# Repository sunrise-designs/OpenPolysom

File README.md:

.png)

OpenPolysom
===========================

This is an open-source Polysomnography (PSG) physical device and analysis software. It performs what is know as a sleep study.

It runs on an ESP32 microcontroller, and collects these signals from a patient:
- [Respiratory Inductance Plethysmography (RIP)](#baseline-removal-from-the-rip-signal---the-chest-belts)
- [Nasal air flow rate](#air-flow-signal-processing)
- RR intervals (heart rate)
- Sound recording for [snoring detection](#snoring-classification-and-feature-extraction)
- Acceleration data from the leg sensors to [detect leg twitching](#accelerometer-data-processing)

New! Some real recordings:
===========================
[A somewhat truncated 2 hours of real sleep data - 17 July 2026](https://polysom.netlify.app/index.html?meta=studies%2Fbiometric_2026-07-16_23-00-00%2Fmeta.json)

Why do this?
===========================
It's about creating an _accessible, rapid_ diagnostic pathway for sleep disorders. Many, many people suffer from sleep disorders, breathing-related ones in particular. They have a significant effect on the quality of life, safety (falling asleep while driving) and serious long-term adverse health effects.
The current diagnostic process is abysmally slow on the NHS. There are private routes, but they are financially prohibitive for most.

It's hard to diagnose because:
- Most of the time, the sufferer is unaware of the problem (they only know they are groggy and tired)
- Partners don't know how to tell "normal" snoring, if there's such a thing, from a serious breathing-related sleep disorder
- It's seen as a "specialist" subject in the NHS, and GPs receive hardly any training in this field. They are quick to dismiss fatigue-related complaints
- Even once the person starts looking for a cause, the different avenues to explore are bewildering, expensive, and full of marketing hype
- There is not a streamlined diagnostic pathway, or "one-size-fits-all" solution, because of individual anatomy, neurological comorbidities, lifestyle and so on

What does this aim to do?
===========================
Firstly, this is not a replacement for a qualified medical opinion and treatment.
However, this seeks to:
- Raise awareness. There's not enough awareness around the variety of sleep disorders in the population. There have been huge campaigns around cancers, heart health (which is fantastic), but not this, yet
- Open source, forever. The main, explicit intention of this project is to always remain fully open source, software and hardware
  This means that anyone with enough knowledge can look at data, contribute, validate and build the OpenPolysom
- It aims to be simple enough for a layman to use, but powerful enough for advanced research and clinical diagnostics
- Affordable. There are great polysomnography solutions out there, sure. But they are very expensive, proprietary, and generally only accessible to
state healthcare systems or private clinics. The goal of this project is to be financially affordable to anyone

What is this going to look like?
===========================
The eventual goal is to have an easy-to-use, reusable, affordable polysomnography device and diagnostic infrastructure.
- A patient receives the device, or even builds it themselves
- They wear it for one or more nights
- Quality pre-processed data is recorded onto the device (removable SD card)
- There could be a few ways to analyze the data:
    - Send it to a specialist doctor or a clinician
    - Ask for advice on peer-to-peer forums like Apnea Board
    - Some combination of local and cloud-based algorithm can detect features of a number of breathing-related sleep disorders, like Obstructive Apnea, Central Apnea, UARS, and so on
- The strength of this project is pulling together various bits of science which are out there, but disjoint and difficult to find and use. It aims to make a comprehensive assessment of the data, find a possible problem (if any) and at least suggest possible treatment pathways. This is in no way a substitute for qualified medical advice.

How can it detect sleep disorders?
===========================
It a basic level, it's not so difficult! (The following is a simplified version!)

- If you're snoring away, then you stop, your chest belts show that you are "paradoxically breathing", in other words heaving for air, but there's no airflow - you might have Obstructive Apnea. You tongue or soft palate have collapsed backwards and blocked your airway. Your blood oxygen will also drop.
- There's no airflow, _and_ the chest belts show no movement. Your brain simply "forgot" to breathe! That's Central Apnea. Your blood oxygen wil also drop.
- Your blood oxygen does not drop appreciably, but your heart rate spikes significantly at times during your sleep. Your body has become quite sensitive to "breathing effort", and even though your airway isn't fully obstructed, your sleep is fragmented enough to make you feel terrible. This might be Upper Airway Resistance Syndrome (UARS). You might a completely "healthy" score on an official sleep apnea scale, but this is still a very serious problem!
- Your breathing might be fine, but you twitch lots in your sleep (this can be detected by an accelerometer). This could be Periodic Limb Movement Disorder (PLMD). This can also make you feel very tired.
- You might have none of the above, but you wake up gasping, talking and screaming in your sleep. You might be suffering from nightmares!
- And so on!

The point it, it takes a confluence of all the different signals recorded by the polysomnography device to steer the diagnosis in the correct direction. Recording just one or two things usually is not enough.

Challenges to solve
===========================
## Medical device compliance

There is no getting around the fact that this is a Medical Device, likely class B. There is no point in simply providing a heap of dry statistics and numerical metrics from the recorded signals - 99% of users without a very specialist skill set would not be able to interpret them. This isn't a "wellness" device. The interpretation is the whole point of the OpenPolysom, being able to cautiously point the user in the right direction on their path to the eventual resolution of their sleep problems.
This lands it firmly in the regulated territory. Therefore, this system, software and hardware alike, will be designed with IEC 62304 (Medical Software) in mind. The intent is to keep the code which extracts the dry metrics completely separate from the code which makes any interpretation of those metrics.

## Accelerometer data processing
I am currently using two accelerometers attached near the ankle to both legs to detect leg twitching and decide whether PLMS (Periodic Limb Movements of Sleep) or PLMD (Periodic Limb Movement Disorder) is present. The American Academy of Sleep Medicine (AASM) scoring criteria are fairly straightforward to interpret, but for an accurate count the acceleration due to twitching (sudden movement followed by return to the same leg position) should be distinguished from the acceleration due to the position change. This will be determined by the angle between the two baseline positions $q1$ and $q2$: $\Delta q = q_2 \otimes q_1^{-1}$ being below a certain threshold. (note: for advanced clinical studies, Leg Movement events are detected with Electromyography (EMG), because isometric contractions which do not result in physical movement also count. The accelerometers is a temporary proxy which is easier to setup and more robust)

## Baseline removal from the RIP signal - the chest belts

The plan is to achieve that using a combination of Qualitative Diagnostic Calibration (QDC) variant (Marvin Sackner, 1989) and Adaptive Iteratively Reweighted Penalized Least Squares (airPLS)

## Snoring classification and feature extraction

The end game would be to achieve accurate classification of anatomical snoring site according to the VOTE (Velum, Oropharynx, Tongue base, and Epiglottis). This could be achieved using MFCC/Mel feature extraction, then a fast real time ML model trained on the MPSSC (Munich-Passau Snore Sound Corpus) data.

## Air flow signal processing

I have not yet recorded a sample signal, but I am guessing there will be pretty standard noise filtering involved

The wiki — an LLM-first knowledge base
===========================
The in-depth documentation lives in an **LLM wiki**: a structured knowledge base written first for AI coding agents to read as working context, and second for humans. It is deliberately [`llms.txt`](https://llmstxt.org/)-shaped — a curated *map* of the project (architecture, data formats, signal processing, settled decisions, roadmap, coding standards) rather than an exhaustive dump — so an agent (or a person) reads the index first and then opens only the pages a task needs. The same Markdown is browsable as a website.

- **Browse it online:** https://sunrise-designs.github.io/OpenPolysom/
- **Read the source:** [`wiki/INDEX.md`](wiki/INDEX.md) — start here
- **Jump straight in:** [architecture](wiki/knowledge/architecture.md) · [data formats](wiki/knowledge/data-formats.md) · [roadmap](wiki/state/roadmap.md)

The Markdown in [`wiki/`](wiki) is rendered to a static site with [Quartz](https://quartz.jzhao.xyz/) and published to GitHub Pages (build: [`web/build.sh`](web/build.sh)).

What hardware does this expect
----------------------------
The hardware is currently a breadboard prototype, however a custom PCB is being developed in Kicad. See [hardware](/Hardware) folder.

The breadboard features (for now)
- LDC1612 inductance-to-frequency sensor on I2C bus with address 0x2B
- SDP800-125Pa Digital DP sensor (±125 Pa) (I2C address 0x25 or 0x26)
- Two MMA8451 accelerometers (with different I2C addresses)
- Polar H9 heart rate sensor via BLE

How to build
----------------------------
This is work in progress as project is developing fast.

The basic dependencies are:
- Python
- npm
- esp-idf (v 6.0 onwards)
- Rust (upcoming)

How to use
----------------------------
See this [brief guide](how%20to%20use.md)

Why a Som?
===========================
"Som" is a shorthand for polysomnography, and "Som" in Russian is a Wels catfish, _Silurus glanis_. I think it looks cool and terrifying in equal measure. Its whiskers also make me think of all the various probes and electrodes which feature on a polysomnography machine.

Disclaimer
===========================
This software is for informational and educational purposes only. It is not a medical device and is not intended to diagnose, treat, cure, or prevent any disease or sleep disorder.

Not Professional Advice: The outputs generated by this software should not be used as a substitute for professional medical advice, diagnosis, or treatment.

Consult a Physician: Always seek the advice of a qualified healthcare provider with any questions you may have regarding a medical condition.

No Liability: The developers and contributors provide this software "as is" and are not responsible for any actions taken based on its results.

References and inspiration
===========================
This software uses (heavily modified)
https://github.com/Seeed-Studio/Seeed_LDC1612

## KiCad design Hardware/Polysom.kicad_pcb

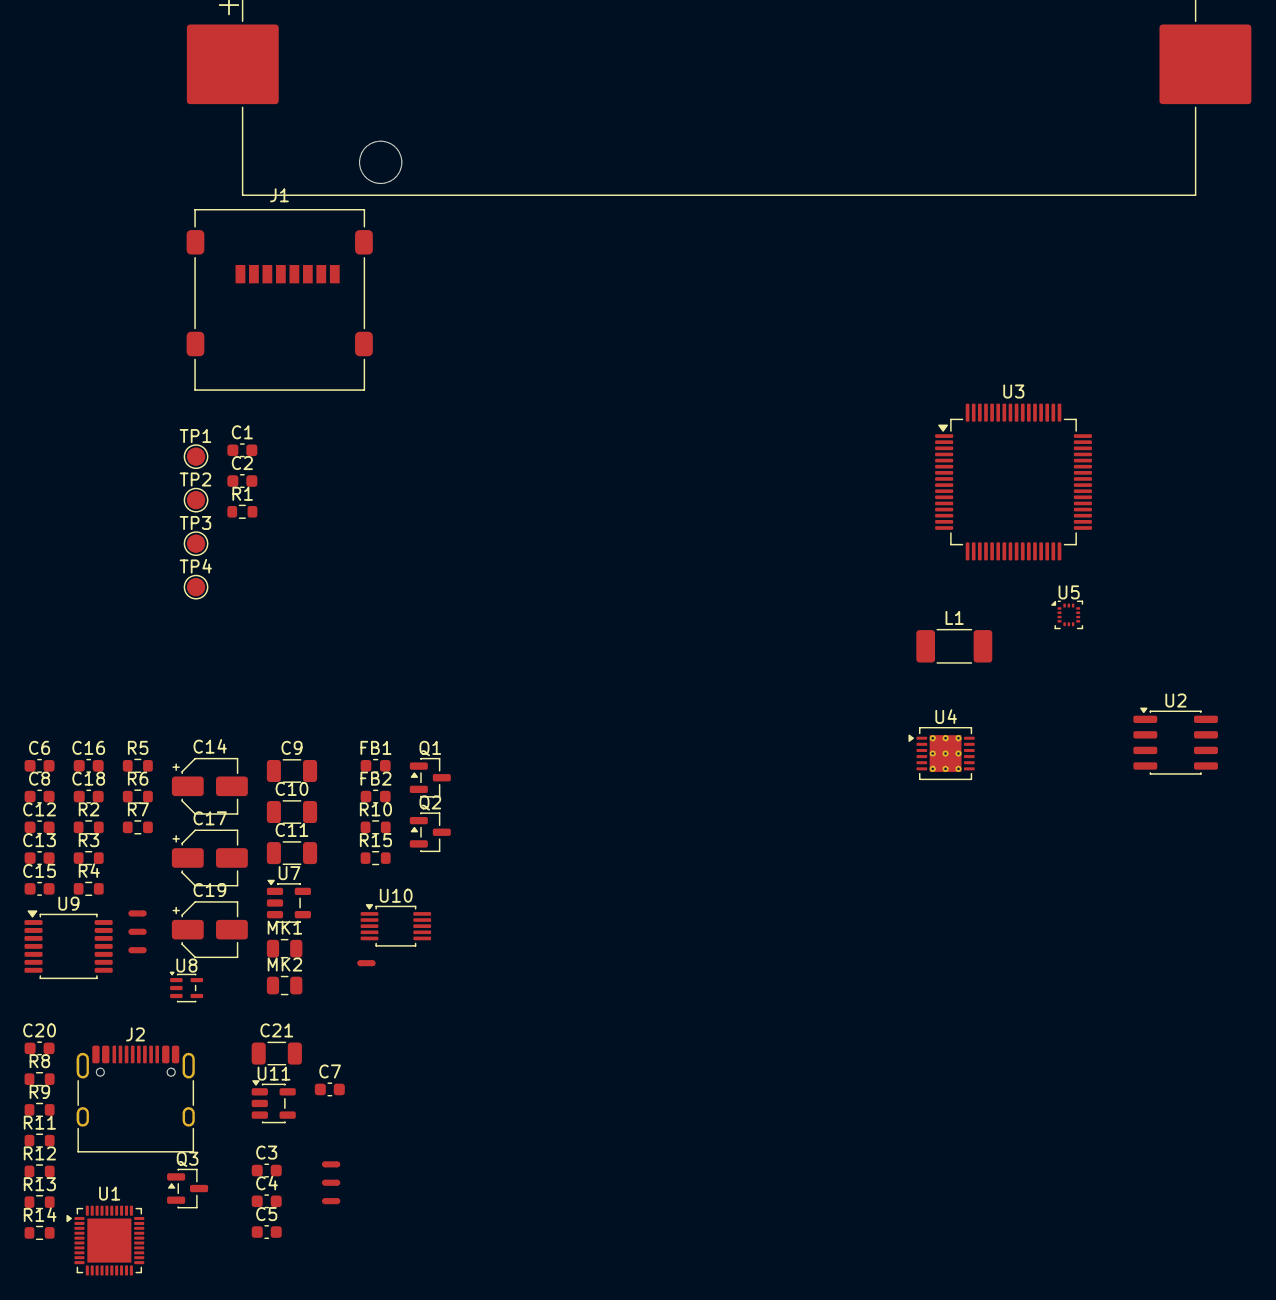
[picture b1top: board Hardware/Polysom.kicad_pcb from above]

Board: 2 copper layers, 68 parts (0 on the bottom side), 42 nets, no tracks yet.

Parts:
BT1: 18650; BatteryHolder_Keystone_1042_1x18650
C1, C2, C12, C13: C; C_0603_1608Metric
C3, C4, C8, C15, C16, C18, C20: 100n; C_0603_1608Metric
C5: 10u; C_0603_1608Metric
C6, C7: 470p; C_0603_1608Metric
C9, C10, C11, C21: 1u; C_1206_3216Metric
C14, C17, C19: 10u; CP_Elec_4x5.4
FB1, FB2: FerriteBead; L_0603_1608Metric
J1: Micro_SD_Card 693072010801; microSD_HC_Molex_47219-2001
J2: USB_C_Receptacle; USB_C_Receptacle_HRO_TYPE-C-31-M-12
L1: L_Chest; L_2010_5025Metric_Pad1.52x2.65mm_HandSolder
MK1, MK2: AOM-5024L-HD-F-R; C_0805_2012Metric
NT1, NT2, NT3, NT4, NT5, NT6, NT7: NetTie_2; NetTie-2_SMD_Pad0.5mm
Q1, Q2, Q3: 2N7002; SOT-23
R1, R8, R9, R10, R13, R14: 10k; R_0603_1608Metric
R2, R3: 1G; R_0603_1608Metric
R4, R5, R6, R7, R15: 100; R_0603_1608Metric
R11, R12: 4K7; R_0603_1608Metric
TP1, TP2, TP3, TP4: TestPoint; TestPoint_Pad_D1.5mm
U1: ESP32-C6; QFN-40-1EP_5x5mm_P0.4mm_EP3.6x3.6mm
U2: OPA1642AID; SOIC-8_3.9x4.9mm_P1.27mm
U3: ADS1299; TQFP-64_10x10mm_P0.5mm
U4: LDC1612; WSON-12-1EP_4x4mm_P0.5mm_EP2.6x3mm_ThermalVias
U5: LIS2DH12TR; LGA-14_2x2mm_P0.35mm_LayoutBorder3x4y
U7, U11: MIC5205-3.3YM5; SOT-23-5
U8: TLV9001IDCK; SOT-353_SC-70-5
U9: PCM1808PWR; TSSOP-14_4.4x5mm_P0.65mm
U10: ADS1115IDGS; TSSOP-10_3x3mm_P0.5mm

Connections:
+3V3: C3.1, C4.1, C5.1, FB1.1, NT5.1 (1_1), R1.2, R10.1, U4.7 (VDD), U5.7 (Vdd_IO), U5.8 (Vdd)
/Accelerometer/SCL: U4.1 (SCL), U5.1 (SCL/SPC), U10.10 (SCL)
/Accelerometer/SDA: U4.2 (SDA), U5.2 (SDA/SDI), U10.9 (SDA)
/EEG/AVDD: U3.19 (AVDD), U3.21 (AVDD), U3.22 (AVDD), U3.54 (AVDD1), U3.56 (AVDD), U3.59 (AVDD), U11.5 (OUT)
/ESP-C6/3V3: C20.1, FB1.2, J1.4 (VDD), R8.1, R9.1, R11.1, R12.1
/ESP-C6/D+: J2.A6 (D+), J2.B6 (D+)
/ESP-C6/D-: J2.A7 (D-), J2.B7 (D-)
/ESP-C6/DAT1: J1.8 (DAT1), R9.2
/ESP-C6/DAT2: J1.1 (DAT2), R8.2
/ESP-C6/VBAT: BT1.1 (+), FB2.2, R13.2
/Microphone/+V: C8.1, C10.1, C16.1, C17.1, U2.8 (V+), U7.5 (OUT), U8.5 (V+), U9.3 (VCC)
/Microphone/VDD: C18.1, C19.1, U9.4 (VDD)
/Microphone/VREF: C14.1, C15.1, U8.1 (+), U9.1 (VREF)
/Microphone/V_GND: C11.1, MK1.1 (-), MK2.1 (-), R2.2, R3.2, U8.3 (-), U8.4
/PERIPH_EN: Q1.1 (G), Q2.3 (D), R15.2, U7.3 (EN), U11.3 (EN)
/RIP/IN0A: C1.1, L1.1, TP1.1 (1_1), U4.9 (IN0A)
/RIP/IN0B: C1.2, L1.2, TP2.1 (1_1), U4.10 (IN0B)
/RIP/IN1A: C2.1, TP3.1 (1_1), U4.11 (IN1A)
/RIP/IN1B: C2.2, TP4.1 (1_1), U4.12 (IN1B)
/SHDN: Q1.3 (D), R10.2, U4.6 (SD)
GND: BT1.2 (-), C3.2, C4.2, C5.2, C6.2, C7.2, C8.2, C9.2, C10.2, C11.2, C14.2, C15.2, C16.2, C17.2, C18.2, C19.2, C20.2, C21.2, J1.6 (VSS), J1.SH (SHIELD), NT1.2, NT2.2, NT3.2, NT4.2, NT6.1 (1_1), NT7.1 (1_1), Q1.2 (S), Q2.2 (S), Q3.2 (S), U1.41 (GND), U2.4 (V-), U3.20 (AVSS), U3.23 (AVSS), U3.32 (AVSS), U3.33 (DGND), U3.49 (DGND), U3.51 (DGND), U3.53 (AVSS1), U3.57 (AVSS), U3.58 (AVSS), U4.3 (CLKIN), U4.8 (GND), U4.13 (GND), U5.3 (SDO), U5.9 (GND), U5.10 (GND), U5.11 (GND), U5.12 (GND), U5.13 (GND), U5.14 (GND), U7.2 (GND), U8.2 (V-), U9.2 (AGND), U9.5 (DGND), U10.3 (GND), U11.2 (GND)
unnamed: J2.A1 (GND), J2.A12 (GND), J2.B1 (GND), J2.B12 (GND)
unnamed: J2.A4 (VBUS), J2.A9 (VBUS), J2.B4 (VBUS), J2.B9 (VBUS)
unnamed: MK1.2 (+), R2.1, R4.2
unnamed: MK2.2 (+), R3.1, R6.2
unnamed: Q3.3 (D), R14.2
unnamed: R13.1, R14.1
unnamed: U1.2 (VDDA3P3), U1.3 (VDDA3P3)
unnamed: R4.1, U2.3 (+)
unnamed: C12.2, R5.2, U2.2 (-)
unnamed: R6.1, U2.5 (+)
unnamed: C13.2, R7.2, U2.6 (-)
unnamed: R1.1, U4.4 (ADDR)
unnamed: C6.1, U7.4 (BP)
unnamed: NT3.1, U9.12 (FMT)
unnamed: NT1.1, U9.10 (MD0)
unnamed: NT2.1, U9.11 (MD1)
unnamed: C12.1, R5.1, U2.1, U9.13 (VIN_L)
unnamed: C13.1, R7.1, U2.7, U9.14 (VIN_R)
unnamed: NT4.1, U10.1 (ADDR)
unnamed: C7.1, U11.4 (BP)
VBAT: C9.1, C21.1, FB2.1, U3.48 (DVDD), U3.50 (DVDD), U7.1 (IN), U10.8 (VDD), U11.1 (IN)

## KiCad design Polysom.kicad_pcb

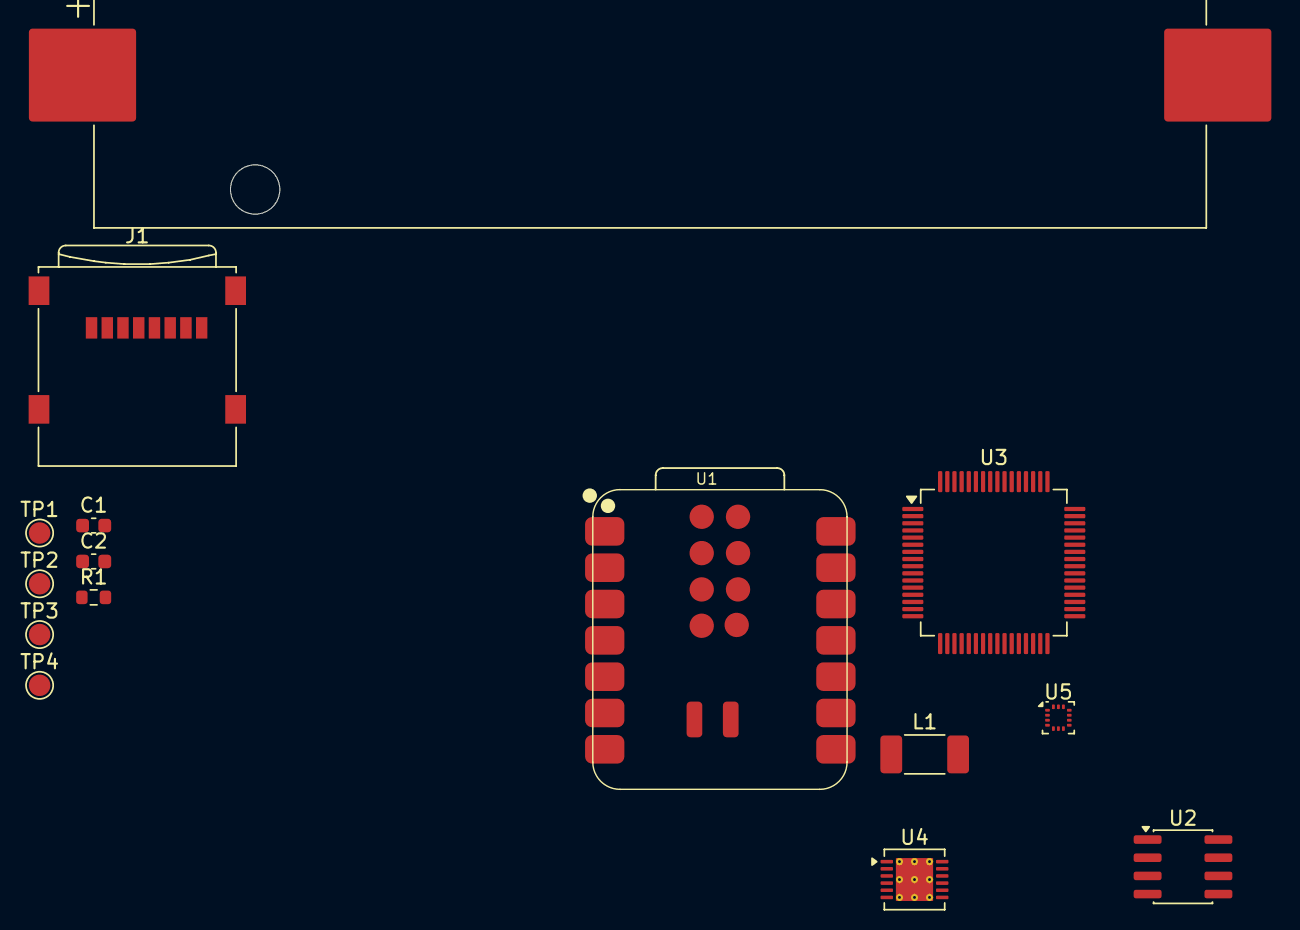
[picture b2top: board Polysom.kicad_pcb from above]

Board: 2 copper layers, 15 parts (0 on the bottom side), 15 nets, no tracks yet.

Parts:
BT1: Battery_Cell; BatteryHolder_Keystone_1042_1x18650
C1, C2: C; C_0603_1608Metric
J1: Micro_SD_Card; microSD_HC_Wuerth_693072010801
L1: L_Trim; L_2010_5025Metric_Pad1.52x2.65mm_HandSolder
R1: 10k; R_0603_1608Metric
TP1, TP2, TP3, TP4: TestPoint; TestPoint_Pad_D1.5mm
U1: Seeed 113991254; XIAO-ESP32-C6-SMD
U2: OPA1642AID; SOIC-8_3.9x4.9mm_P1.27mm
U3: ADS1299; TQFP-64_10x10mm_P0.5mm
U4: LDC1612; WSON-12-1EP_4x4mm_P0.5mm_EP2.6x3mm_ThermalVias
U5: LIS2DH12TR; LGA-14_2x2mm_P0.35mm_LayoutBorder3x4y

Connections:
/Accelerometer/SCL: U1.6 (GPIO23_D5_SCL), U4.1 (SCL), U5.1 (SCL/SPC)
/Accelerometer/SDA: U1.5 (GPIO22_D4_SDA), U4.2 (SDA), U5.2 (SDA/SDI)
/RIP/GND: U4.3 (CLKIN), U4.8 (GND), U4.13 (GND)
/RIP/IN0A: C1.1, L1.1, TP1.1 (1_1), U4.9 (IN0A)
/RIP/IN0B: C1.2, L1.2, TP2.1 (1_1), U4.10 (IN0B)
/RIP/IN1A: C2.1, TP3.1 (1_1), U4.11 (IN1A)
/RIP/IN1B: C2.2, TP4.1 (1_1), U4.12 (IN1B)
/RIP/VDD: R1.2, U4.7 (VDD)
GND: BT1.2 (-), U2.4 (V-)
unnamed: U3.19 (AVDD), U3.21 (AVDD), U3.22 (AVDD), U3.56 (AVDD), U3.59 (AVDD)
unnamed: U3.20 (AVSS), U3.23 (AVSS), U3.32 (AVSS), U3.57 (AVSS), U3.58 (AVSS)
unnamed: U3.33 (DGND), U3.49 (DGND), U3.51 (DGND)
unnamed: U3.48 (DVDD), U3.50 (DVDD)
unnamed: R1.1, U4.4 (ADDR)
unnamed: U5.9 (GND), U5.10 (GND), U5.11 (GND), U5.12 (GND), U5.13 (GND), U5.14 (GND)

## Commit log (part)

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2026-04-07 top-level structure and ESP32-C6 pin assignments nearly sorted
2026-04-09 text comments sections added
2026-04-11 added everything to repo
2026-04-11 won't be using this, as it does not have enough pins
2026-04-12 some work on sch and docs added
2026-04-24 v0: Fresh start, new project identity
2026-06-15 rpi5 pinout
2026-06-15 AD8232 interface via ESP32-S3 added
2026-06-15 AD8232 heart rate reading added
2026-06-15 moved the Arduino sketch into it's own folder, removed Python code, ESP32 now reads the BLE data directly from the Polar H9 heart rate sensor
2026-06-15 correct to 10 byte I2C packet
2026-06-15 readme etc
2026-06-15 always get HR changes from I2C buffer
2026-06-15 matlab plotting added
2026-06-15 erase file contents
2026-06-15 now prints accel values
2026-06-15 saving to ESP32 instead
2026-06-15 no print during dumping
2026-06-15 trying to read I2C but no luck. Will store on ESP32 instead
2026-06-15 can read the file back now via "D" command
2026-06-15 excellent. I think this is working
2026-06-16 html plotting added
2026-06-16 erase added
2026-06-17 shifting baseline removal implemented. Signal looks good
2026-06-17 Signal processing added and refactored - LM and PLMs per American Academy of sleep medicine, HRV. Refactored into separate files. Plotly looks really good
2026-06-17 make sure that the index.html is rendered correctly
2026-06-17 report generation uses a two format pipeline: pdf via matplotlib (zero other dependencies) and html via plotly (much better web rendering)
2026-06-17 ESP32 code refactored, and writes EDF file instead. I need to think about how best to manage file storage. I might utilise separate run-time compressed files for each metric, and assemble them into E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
2026-06-17 text in the webpage now selectable
2026-06-18 first echarts html export. looks good!
2026-06-19 does not work yet, but a good milestone for introducing a .zarr based contract between the signal processing and charting modules (the latter is now in TS)
2026-06-19 Fix for the zarr export
2026-06-19 web deployment updated - seems to work! Hooray!
2026-06-19 questions!
2026-06-19 tidy up and some raw data to try the code
2026-06-19 moving obsolete things around
2026-06-19 Add LLM wiki for the data pipeline (component 2)
    Seed an llms.txt-style knowledge base under wiki/ documenting the settled component-2 architecture: C++ ingest, Python processing, and a TypeScript web app, with Zarr + JSON metadata as the language-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
2026-06-19 Host the wiki via Quartz + GitHub Pages
    Add a Quartz v5 build (web/build.sh + web/quartz.config.yaml, adapted from the ens-labs-wiki setup) that renders wiki/ into a static site, and a deploy-pages GitHub Actions workflow that builds on PR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
2026-06-20 Tremor-Illustrated viewer: zarrita reader, per-channel bubble charts, Zarr fixture + tests, PWA
    src_web:
    - Scaffold to coding standards: pnpm, strict tsconfig, flat ESLint (functional rules), Vitest
    - Migrate zarr.js -> zarrita.js; read Zarr v2 + Blosc(zstd) over the boundary (WASM decode)
    - Tremor-Illustrated UI: per-channel "bubble" cards (own y-axis + time axis, full-width),
    data-driven PLMI gauge, KPI cards, montage rail; mobile tap-to-fullscreen (landscape) + touch-scroll
    - PWA: manifest, service worker (offline), icons
2026-06-21 Enforce discipline: Husky hooks + ESLint functional pass
    ESLint green (0 problems):
    - functional-core rules (no-let, immutable-data, prefer-readonly-type,
    prefer-readonly-parameter-types) stay strict on the pure core
    (format / narrative / tokens / types)
    - scoped override relaxes them on the DOM/ECharts/Zarr I/O edge + tests
    (typed-array / DOM / option params, chart lifecycle)
2026-06-21 Tighten viewer UI: squarer corners + full-width bubble charts
    - border radius 14 -> 4px (cards read near-square; pills unchanged)
    - per-bubble chart margins tightened (grid left/right 50/14 -> 38/8) and card
    side padding 12 -> 6px, so each waveform uses the full bubble width and the
    x-axis end label is visible
    - rebuilt bundle; bumped asset cache-bust
2026-06-23 Desktop viewer: taller charts + don't capture the wheel
    - double the per-channel plot height on desktop/tablet (.sig-plot 150 -> 300px;
    mobile <=760px stays 132px)
    - disable the inside-zoom wheel/drag capture on desktop so the page scrolls
    normally with the cursor over a chart (zoomOnMouseWheel / moveOnMouseWheel /
    moveOnMouseMove = false); crosshair + tooltip sync via axisPointer +
    echarts.connect is unaffected
2026-06-24 Docker script to make sure that everything builds on a clean machine
2026-06-24 added some useful json files to the repo that were previously ignored
2026-06-24 merging hardware (in Kicad) into this repo. They are very closely tied together, and share a lot of knowledge
2026-06-24 updated readme to reflect the evolution of the project
2026-06-24 this should build from the root now
2026-06-24 Fix wiki site after repo rename; explain the LLM wiki in the README
    The repo was renamed ProtoSom -> OpenPolysom, which left the Quartz build's
    baseUrl/basepath stale, so the explorer, graph, search and SPA navigation all
    linked to /ProtoSom/* and 404'd.
    - web/quartz.config.yaml: baseUrl -> sunrise-designs.github.io/OpenPolysom (this
    path sets the SPA basepath + the in-site link prefix, so it must match the repo
    name); footer GitHub link -> OpenPolysom
2026-06-24 Unbreak the Husky hooks: run checks only when their tooling is installed
    Dmitry's minimal package.json (pnpm->npm) dropped lint-staged and the test script, but the committed hooks still called them, so every commit/push failed repo-wide. Make both hooks package-manager-ag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
2026-06-24 change the title to reflect Hardware now being a part of this central repo - which is now OpenPolysom
2026-06-24 add missing npm zarrita dependency
2026-06-24 another readme update to reality
2026-06-24 remove old heart rate acquisition method
2026-06-25 ported to ESP32-C6 target
2026-06-25 hardware datasheets committed to the repo
2026-06-26 some new datasheets for the ESP32-C6 dev board
2026-06-26 some EEG hardware options added, like DIN 42802-1 1.5mm plugs and sockets
2026-06-26 ESP32-S3 code is now obsolete
2026-06-26 port
2026-06-28 inital ESP config
2026-06-28 esp32 code fixes - builds now with idf 6.0.1
2026-06-28 separated into invididual ESP components - builds
2026-06-28 ignore the reference code for the LCD example
2026-06-28 harmonise with the example code
2026-06-28 remove redundant files
2026-06-28 refactoring to store all pin settings in Kconfig, and decouple the display components from dependency on sensor code
2026-06-28 remove redunant code which reads out files over UART - they are getting far too large, and we now store them on an SD card for direct read-out on the PC
2026-06-28 refactor sensors into their individual device files
